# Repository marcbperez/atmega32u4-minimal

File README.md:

# atmega32u4-minimal

Expansion board for Atmega32u4.

## Installation

The schematics project is done in KiCad, free and available to most common
platforms. More information on how to download and install KiCad can be found in
its [official download page][download-kicad].

## Usage

Clone the sources and browse the package folder. The KiCad project is located in
`kicad-project/atmega32u4-minimal.pro`.

```bash
git clone https://github.com/marcbperez/atmega32u4-minimal
cd atmega32u4-minimal
```

## Testing

There is no testing in place for this project yet.

## Troubleshooting

The [issue tracker][issue-tracker] intends to manage and compile bugs,
enhancements, proposals and tasks. Reading through its material or reporting to
its contributors via the platform is strongly recommended.

## Contributing

This project adheres to [Semantic Versioning][semver] and to certain syntax
conventions defined in [.editorconfig][editorconfig]. To get a list of changes
refer to the [CHANGELOG][changelog]. Only branches prefixed by *feature-*,
*hotfix-*, or *release-* will be considered:

  - Fork the project.
  - Create your new branch: `git checkout -b feature-my-feature develop`
  - Commit your changes: `git commit -am 'Added my new feature.'`
  - Push the branch: `git push origin feature-my-feature`
  - Submit a pull request.

## Credits

This project is created by [marcbperez][author] and maintained by its
[author][author] and contributors.

## License

This project is licensed under the [Apache License Version 2.0][license].

[author]: https://marcbperez.github.io
[issue-tracker]: https://github.com/marcbperez/atmega32u4-minimal/issues
[editorconfig]: .editorconfig
[changelog]: CHANGELOG.md
[license]: LICENSE
[semver]: http://semver.org
[download-kicad]: http://kicad-pcb.org/download/

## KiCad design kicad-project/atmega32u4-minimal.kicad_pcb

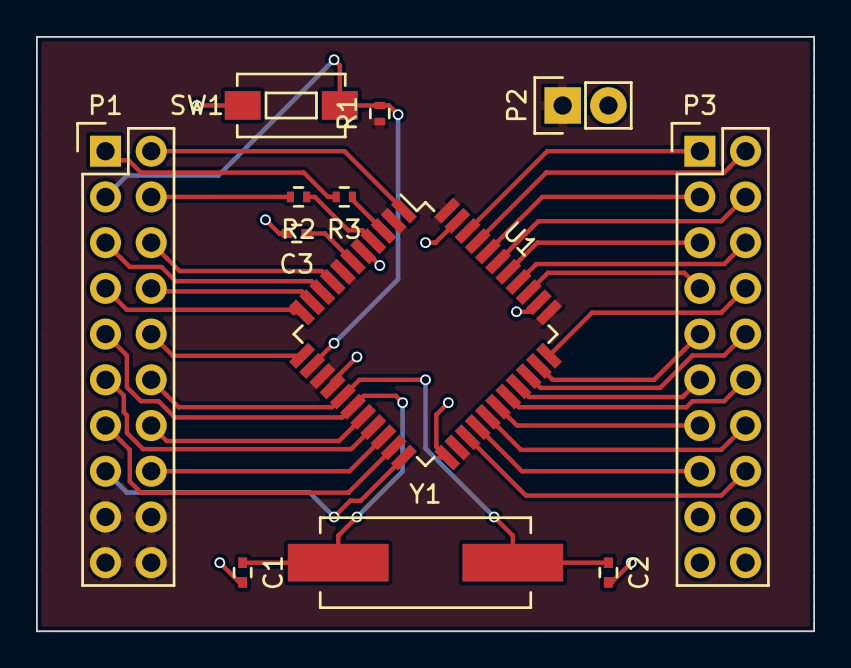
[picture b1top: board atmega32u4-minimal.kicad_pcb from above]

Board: 2 copper layers, 43.2 x 33.0 mm, 12 parts (0 on the bottom side), 37 nets.

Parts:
C1, C2, C3: C; C_0402
P1, P3: CONN_02X10; Pin_Header_Straight_2x10
P2: CONN_01X02; Pin_Header_Straight_1x02
R1, R2, R3: R; R_0402
SW1: SW_PUSH; SW_SPST_EVQPE1
U1: ATmega32U4; TQFP-44_10x10mm_Pitch0.8mm
Y1: Crystal; Crystal_HC49-SD_SMD

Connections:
+5V: P1.17, P1.18, P1.19, P1.20, P2.1, R1.1, U1.2, U1.7, U1.14, U1.24, U1.34, U1.44
/AREF: P3.1, U1.42
/D+: R2.1, U1.4
/D-: R3.1, U1.3
/PB0: P1.6, U1.8
/PB1: P1.5, U1.9
/PB2: P1.8, U1.10
/PB3: P1.7, U1.11
/PB4: P3.13, U1.28
/PB5: P3.12, U1.29
/PB6: P3.11, U1.30
/PB7: P1.10, U1.12
/PC6: P3.10, U1.31
/PC7: P3.9, U1.32
/PD0: P1.14, U1.18
/PD1: P1.11, U1.19
/PD2: P1.16, U1.20
/PD3: P1.13, U1.21
/PD4: P3.16, U1.25
/PD5: P1.15, U1.22
/PD6: P3.15, U1.26
/PD7: P3.14, U1.27
/PE2: P3.8, U1.33
/PE6: P1.2, U1.1
/PF0: P3.2, U1.41
/PF1: P3.3, U1.40
/PF4: P3.4, U1.39
/PF5: P3.5, U1.38
/PF6: P3.6, U1.37
/PF7: P3.7, U1.36
/RESET: P1.3, R1.2, SW1.2, U1.13
/UCAP: C3.1, U1.6
/USBD+: P1.4, R2.2
/USBD-: P1.1, R3.2
/XTAL1: C1.1, P1.9, U1.17, Y1.2
/XTAL2: C2.1, P1.12, U1.16, Y1.1
GND: C1.2, C2.2, C3.2, P2.2, P3.17, P3.18, P3.19, P3.20, SW1.1, U1.5, U1.15, U1.23, U1.35, U1.43

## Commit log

2017-09-04 Added ignore list for untracked resources.
2017-09-07 Added a README which covers project description and usage.
2017-09-07 Added a LICENSE file to define project ownership and rights.
2017-09-07 Added this CHANGELOG file to document project changes and versions.
2017-09-07 Added an EditorConfig to suggest syntax and format standards.
2017-09-07 Added a .gitignore list for untracked resources.
2017-09-09 Bumped version to 0.1.0.
2017-10-01 PCB backup to Git ignore list.
2017-10-01 Included unreleased changes.
2017-10-01 Added PDFs for the PCB and schematics.
2017-10-01 Added KiCad project, PCB and schematics design.
2017-10-02 Bumped version to 0.2.0.
2017-10-03 Bumped version to 0.2.1.
2017-10-03 Fixed missing component values.
